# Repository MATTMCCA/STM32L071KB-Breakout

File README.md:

# STM32L071KB-Breakout
 STM32L071KB Breakout/Eval Board & STLink V2 adapter.
 
*Was quickly thrown together to further private works.*

**Gerbers meet JLC design spec**
 
 ## BOM
* EVAL 

[Digikey Cart Share](https://www.digikey.com/short/h47hrp48)

[Board](https://oshpark.com/shared_projects/n7sNnrIe)

* PROG 

[Digikey Cart Share](https://www.digikey.com/short/nmdddnm9)

[Board](https://oshpark.com/shared_projects/kYvOD2Zq)

---
### Captains Log (star date.. too cloudy, can't tell)

Boards came back from fab, they look good, just waiting on parts....

Parts came today, everything's working just fine.

### Borrowed works maintain original license.

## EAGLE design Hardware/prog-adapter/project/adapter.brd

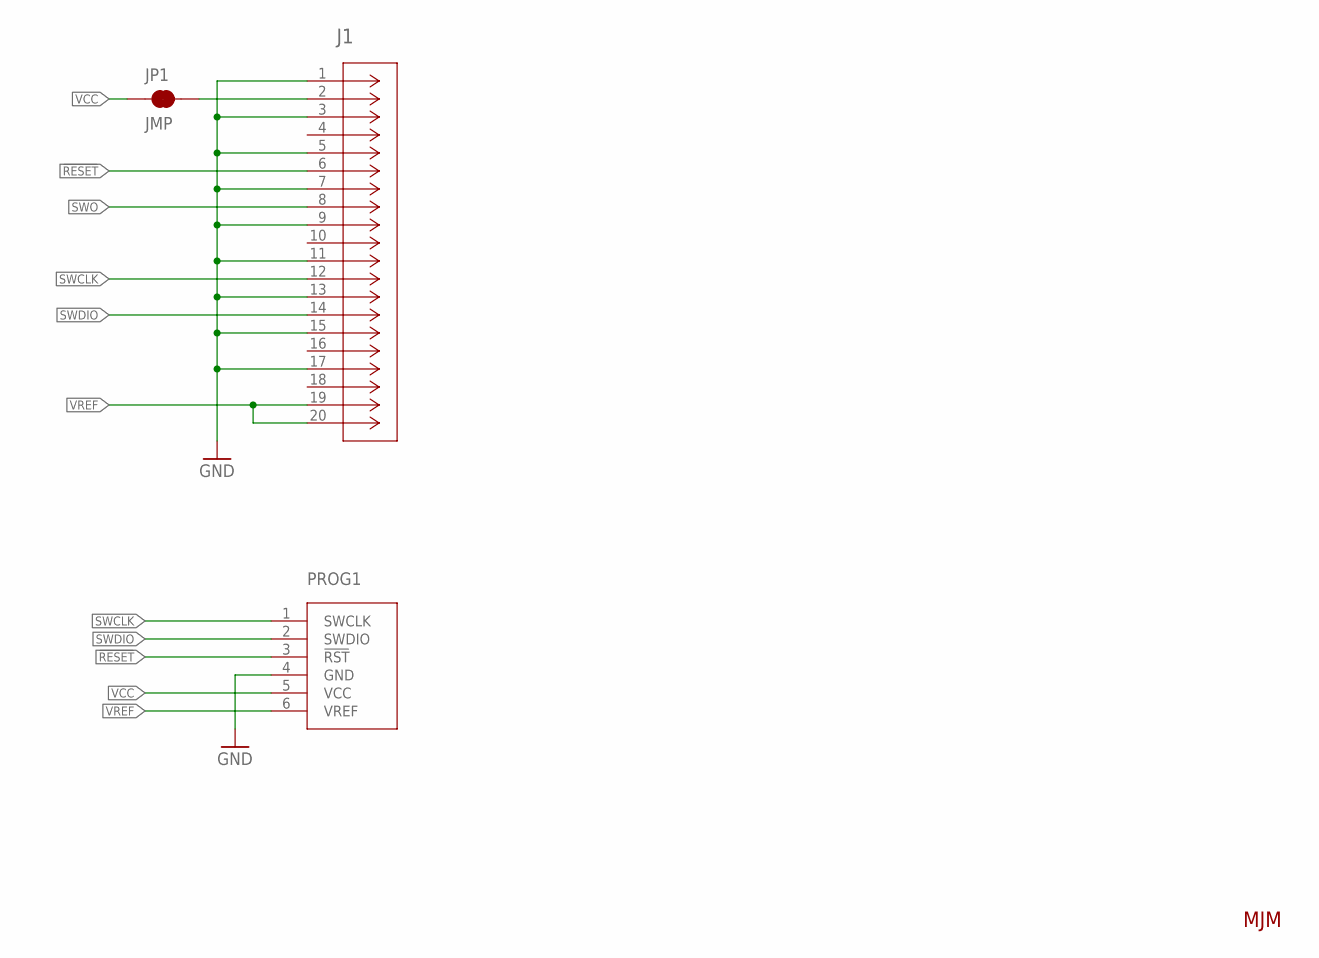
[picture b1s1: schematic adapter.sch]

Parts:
J1: SFH11-PBPC-D10-ST-BK; CONN_SFH11-PBPC-D10-ST-BK_SUL
JP1: JMP; SMT-JUMPER_2_NC_TRACE_SILK
PROG1: 0532610671_OP; 0532610671

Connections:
!RESET: J1.6, PROG1.3 (!RST)
GND: J1.1, J1.3, J1.5, J1.7, J1.9, J1.11, J1.13, J1.15, J1.17, PROG1.4 (GND)
unnamed: J1.2, JP1.2
SWCLK: J1.12, PROG1.1 (SWCLK)
SWDIO: J1.14, PROG1.2 (SWDIO)
SWO: J1.8
VCC: JP1.1, PROG1.5 (VCC)
VREF: J1.19, J1.20, PROG1.6 (VREF)

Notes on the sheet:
MJM

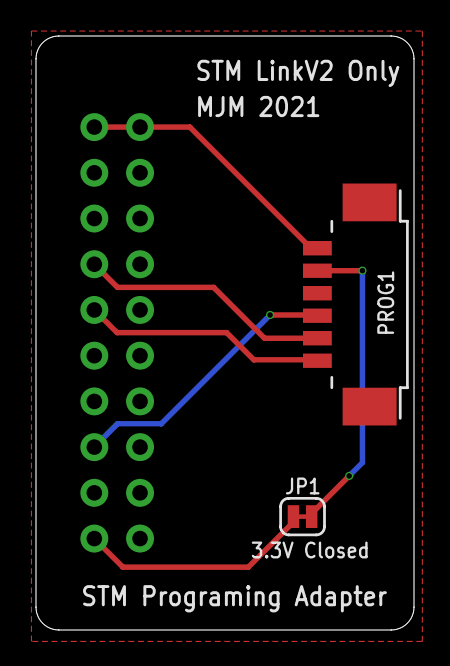
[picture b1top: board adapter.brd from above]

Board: 2 copper layers, 21.0 x 33.0 mm, 3 parts (1 on the bottom side), 7 nets.

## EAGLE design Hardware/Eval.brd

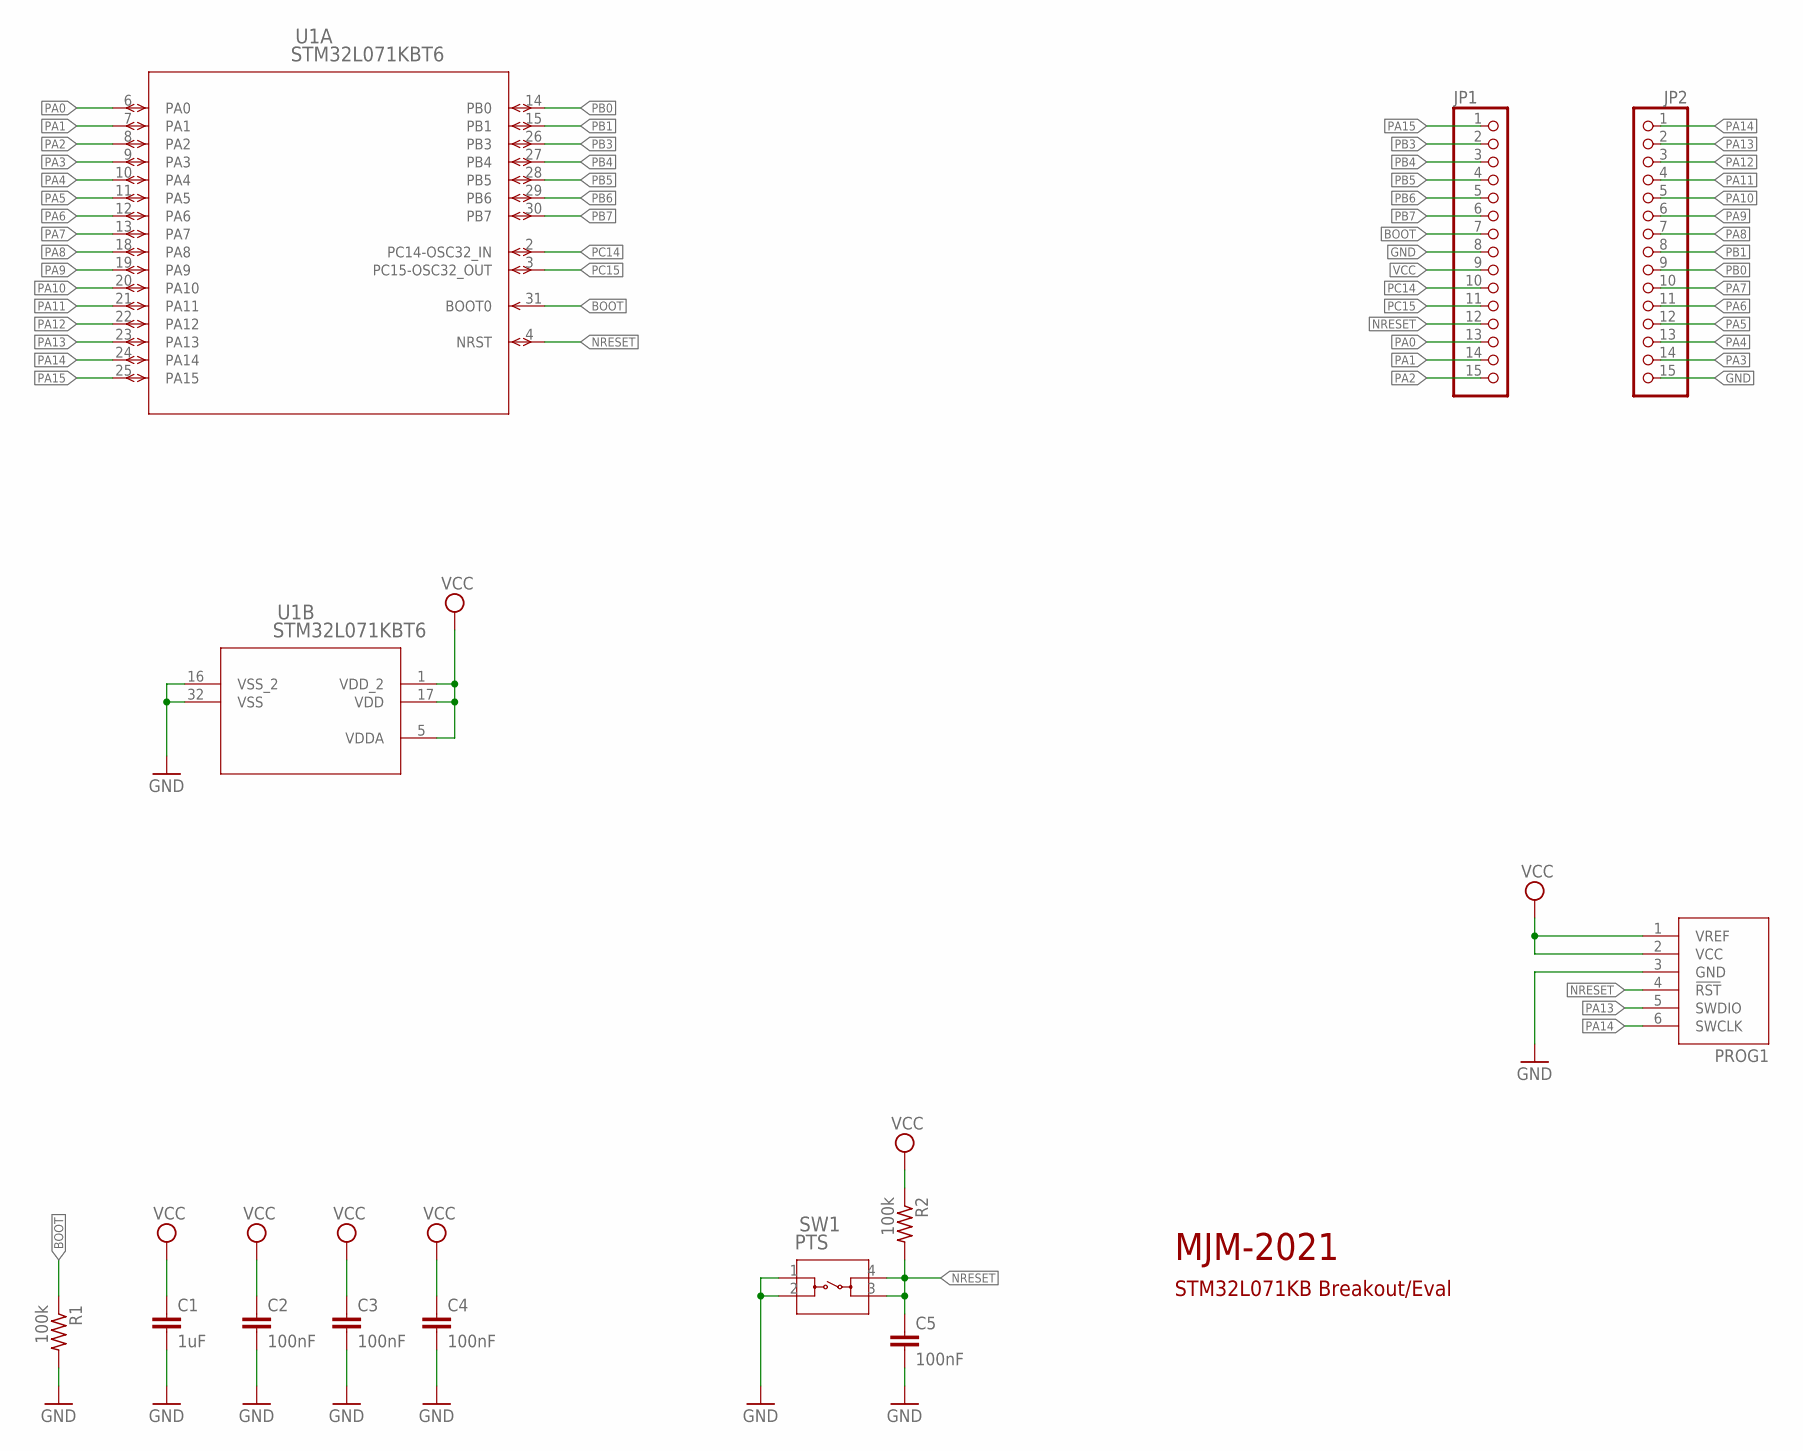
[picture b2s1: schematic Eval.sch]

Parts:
C1: 1uF; C0603
C2, C3, C4, C5: 100nF; C0603
JP1, JP2: PINHD-1X15; 1X15
PROG1: 0532610671
R1, R2: 100k; R0603
SW1: PTS; PTS_647_SN50_SMTR2_LFS-M
U1: STM32L071KBT6; LQFP32_7X7X1P4

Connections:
BOOT: JP1.7, R1.1, U1.31 (BOOT0)
GND: C1.2, C2.2, C3.2, C4.2, C5.2, JP1.8, JP2.15, PROG1.3 (GND), R1.2, SW1.1, SW1.2, U1.16 (VSS_2), U1.32 (VSS)
NRESET: C5.1, JP1.12, PROG1.4 (!RST), R2.2, SW1.3, SW1.4, U1.4 (NRST)
PA0: JP1.13, U1.6 (PA0)
PA1: JP1.14, U1.7 (PA1)
PA2: JP1.15, U1.8 (PA2)
PA3: JP2.14, U1.9 (PA3)
PA4: JP2.13, U1.10 (PA4)
PA5: JP2.12, U1.11 (PA5)
PA6: JP2.11, U1.12 (PA6)
PA7: JP2.10, U1.13 (PA7)
PA8: JP2.7, U1.18 (PA8)
PA9: JP2.6, U1.19 (PA9)
PA10: JP2.5, U1.20 (PA10)
PA11: JP2.4, U1.21 (PA11)
PA12: JP2.3, U1.22 (PA12)
PA13: JP2.2, PROG1.5 (SWDIO), U1.23 (PA13)
PA14: JP2.1, PROG1.6 (SWCLK), U1.24 (PA14)
PA15: JP1.1, U1.25 (PA15)
PB0: JP2.9, U1.14 (PB0)
PB1: JP2.8, U1.15 (PB1)
PB3: JP1.2, U1.26 (PB3)
PB4: JP1.3, U1.27 (PB4)
PB5: JP1.4, U1.28 (PB5)
PB6: JP1.5, U1.29 (PB6)
PB7: JP1.6, U1.30 (PB7)
PC14: JP1.10, U1.2 (PC14-OSC32_IN)
PC15: JP1.11, U1.3 (PC15-OSC32_OUT)
VCC: C1.1, C2.1, C3.1, C4.1, JP1.9, PROG1.1 (VREF), PROG1.2 (VCC), R2.1, U1.1 (VDD_2), U1.5 (VDDA), U1.17 (VDD)

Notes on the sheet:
MJM-2021
STM32L071KB Breakout/Eval

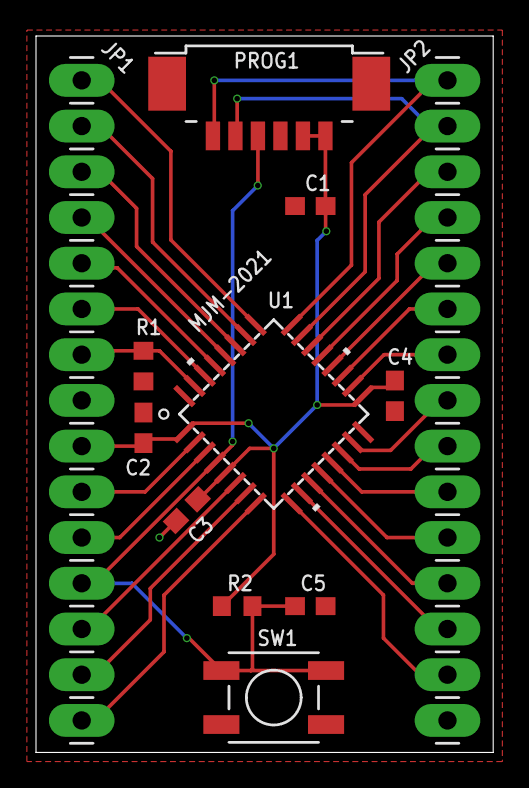
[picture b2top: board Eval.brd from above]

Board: 2 copper layers, 25.4 x 39.8 mm, 12 parts (0 on the bottom side), 29 nets.

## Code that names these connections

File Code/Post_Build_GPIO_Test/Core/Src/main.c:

/* USER CODE BEGIN Header */

/*
 * MJM Post Build Test Code for GPIO
 * 2021
 *
 */

/**
  ******************************************************************************
  * @file           : main.c
  * @brief          : Main program body
  ******************************************************************************
  * @attention
  *
  * <h2><center>&copy; Copyright (c) 2021 STMicroelectronics.
  * All rights reserved.</center></h2>
  *
  * This software component is licensed by ST under BSD 3-Clause license,
  * the "License"; You may not use this file except in compliance with the
  * License. You may obtain a copy of the License at:
  *                        opensource.org/licenses/BSD-3-Clause
  *
  ******************************************************************************
  */
/* USER CODE END Header */
/* Includes ------------------------------------------------------------------*/
#include "main.h"
#include "gpio.h"

/* Private includes ----------------------------------------------------------*/
/* USER CODE BEGIN Includes */

/* USER CODE END Includes */

/* Private typedef -----------------------------------------------------------*/
/* USER CODE BEGIN PTD */

typedef struct {
	GPIO_TypeDef *GPIOx;
	uint16_t GPIO_Pin;
} pinmap;

/* USER CODE END PTD */

/* Private define ------------------------------------------------------------*/
/* USER CODE BEGIN PD */
/* USER CODE END PD */

/* Private macro -------------------------------------------------------------*/
/* USER CODE BEGIN PM */

/* USER CODE END PM */

/* Private variables ---------------------------------------------------------*/

/* USER CODE BEGIN PV */

/* USER CODE END PV */

/* Private function prototypes -----------------------------------------------*/
void SystemClock_Config(void);
/* USER CODE BEGIN PFP */

/* USER CODE END PFP */

/* Private user code ---------------------------------------------------------*/
/* USER CODE BEGIN 0 */

/* USER CODE END 0 */

/**
  * @brief  The application entry point.
  * @retval int
  */
int main(void)
{
  /* USER CODE BEGIN 1 */

  /* USER CODE END 1 */

  /* MCU Configuration--------------------------------------------------------*/

  /* Reset of all peripherals, Initializes the Flash interface and the Systick. */
  HAL_Init();

  /* USER CODE BEGIN Init */

  /* USER CODE END Init */

  /* Configure the system clock */
  SystemClock_Config();

  /* USER CODE BEGIN SysInit */

  /* USER CODE END SysInit */

  /* Initialize all configured peripherals */
  MX_GPIO_Init();
  /* USER CODE BEGIN 2 */


  /* TEST GPIO STRUCT ARRAY */
  pinmap pm[23] =
  {
	  {PIN_PA0_GPIO_Port,  PIN_PA0_Pin},
	  {PIN_PA1_GPIO_Port,  PIN_PA1_Pin},
	  {PIN_PA2_GPIO_Port,  PIN_PA2_Pin},
	  {PIN_PA3_GPIO_Port,  PIN_PA3_Pin},
	  {PIN_PA4_GPIO_Port,  PIN_PA4_Pin},
	  {PIN_PA5_GPIO_Port,  PIN_PA5_Pin},
	  {PIN_PA6_GPIO_Port,  PIN_PA6_Pin},
	  {PIN_PA7_GPIO_Port,  PIN_PA7_Pin},
	  {PIN_PA8_GPIO_Port,  PIN_PA8_Pin},
	  {PIN_PA9_GPIO_Port,  PIN_PA9_Pin},
	  {PIN_PA10_GPIO_Port, PIN_PA10_Pin},
	  {PIN_PA11_GPIO_Port, PIN_PA11_Pin},
	  {PIN_PA12_GPIO_Port, PIN_PA12_Pin},
	  //{PIN_PA13_GPIO_Port, PIN_PA13_Pin},
	  //{PIN_PA14_GPIO_Port, PIN_PA14_Pin},
	  {PIN_PA15_GPIO_Port, PIN_PA15_Pin},
	  {PIN_PB0_GPIO_Port,  PIN_PB0_Pin},
	  {PIN_PB1_GPIO_Port,  PIN_PB1_Pin},
	  {PIN_PB3_GPIO_Port,  PIN_PB3_Pin},
	  {PIN_PB4_GPIO_Port,  PIN_PB4_Pin},
	  {PIN_PB5_GPIO_Port,  PIN_PB5_Pin},
	  {PIN_PB6_GPIO_Port,  PIN_PB6_Pin},
	  {PIN_PB7_GPIO_Port,  PIN_PB7_Pin},
	  {PIN_PC14_GPIO_Port, PIN_PC14_Pin},
	  {PIN_PC15_GPIO_Port, PIN_PC15_Pin},
  };

  /* USER CODE END 2 */

  /* Infinite loop */
  /* USER CODE BEGIN WHILE */
  while (1)
  {
    /* USER CODE END WHILE */

    /* USER CODE BEGIN 3 */

	  for(int i = 0; i < 23; i++) {
		  HAL_GPIO_TogglePin(pm[i].GPIOx, pm[i].GPIO_Pin); //should toggle all pins forever
		  __NOP(); //add breakpoint
	  }

  }
  /* USER CODE END 3 */
}

/**
  * @brief System Clock Configuration
  * @retval None
  */
void SystemClock_Config(void)
{
  RCC_OscInitTypeDef RCC_OscInitStruct = {0};
  RCC_ClkInitTypeDef RCC_ClkInitStruct = {0};

  /** Configure the main internal regulator output voltage
  */
  __HAL_PWR_VOLTAGESCALING_CONFIG(PWR_REGULATOR_VOLTAGE_SCALE1);
  /** Initializes the RCC Oscillators according to the specified parameters
  * in the RCC_OscInitTypeDef structure.
  */
  RCC_OscInitStruct.OscillatorType = RCC_OSCILLATORTYPE_HSI;
  RCC_OscInitStruct.HSIState = RCC_HSI_ON;
  RCC_OscInitStruct.HSICalibrationValue = RCC_HSICALIBRATION_DEFAULT;
  RCC_OscInitStruct.PLL.PLLState = RCC_PLL_ON;
  RCC_OscInitStruct.PLL.PLLSource = RCC_PLLSOURCE_HSI;
  RCC_OscInitStruct.PLL.PLLMUL = RCC_PLLMUL_4;
  RCC_OscInitStruct.PLL.PLLDIV = RCC_PLLDIV_2;
  if (HAL_RCC_OscConfig(&RCC_OscInitStruct) != HAL_OK)
  {
    Error_Handler();
  }
  /** Initializes the CPU, AHB and APB buses clocks
  */
  RCC_ClkInitStruct.ClockType = RCC_CLOCKTYPE_HCLK|RCC_CLOCKTYPE_SYSCLK
                              |RCC_CLOCKTYPE_PCLK1|RCC_CLOCKTYPE_PCLK2;
  RCC_ClkInitStruct.SYSCLKSource = RCC_SYSCLKSOURCE_PLLCLK;
  RCC_ClkInitStruct.AHBCLKDivider = RCC_SYSCLK_DIV1;
  RCC_ClkInitStruct.APB1CLKDivider = RCC_HCLK_DIV1;
  RCC_ClkInitStruct.APB2CLKDivider = RCC_HCLK_DIV1;

  if (HAL_RCC_ClockConfig(&RCC_ClkInitStruct, FLASH_LATENCY_1) != HAL_OK)
  {
    Error_Handler();
  }
}

/* USER CODE BEGIN 4 */

/* USER CODE END 4 */

/**
  * @brief  This function is executed in case of error occurrence.
  * @retval None
  */
void Error_Handler(void)
{
  /* USER CODE BEGIN Error_Handler_Debug */
  /* User can add his own implementation to report the HAL error return state */
  __disable_irq();
  while (1)
  {
  }
  /* USER CODE END Error_Handler_Debug */
}

#ifdef  USE_FULL_ASSERT
/**
  * @brief  Reports the name of the source file and the source line number
  *         where the assert_param error has occurred.
  * @param  file: pointer to the source file name
  * @param  line: assert_param error line source number
  * @retval None
  */
void assert_failed(uint8_t *file, uint32_t line)
{
  /* USER CODE BEGIN 6 */
  /* User can add his own implementation to report the file name and line number,
     ex: printf("Wrong parameters value: file %s on line %d\r\n", file, line) */
  /* USER CODE END 6 */
}
#endif /* USE_FULL_ASSERT */

/************************ (C) COPYRIGHT STMicroelectronics *****END OF FILE****/

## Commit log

2021-08-22 init
2021-08-22 added adapter board
    Changed repo struct.
    Added prog_adapter.
2021-08-22 step upload
2021-08-22 GPIO TEST
    Post assembly GPIO Test Code.
2021-08-22 enabled single wire debugging on pa13 & pa14
2021-08-22 derp
    index=i, !0
2021-08-30 spell check fail

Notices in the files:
parts and their libraries:
COPYRIGHT: Copyright (C) 2018 Accelerated Designs. All rights reserved
SparkFun-Jumpers: Licensing: Creative Commons ShareAlike 4.0 International - https://creativecommons.org/licenses/by-sa/4.0
